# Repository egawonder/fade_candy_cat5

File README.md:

# fade_candy_cat5

When building the pirate ship bar I wanted to run RGB LEDs all around the ship.  Of course, this didn't initially work because of SI issues. I used braided pairs to solve this but thought there's got to be a better way.  This is the 80% better way. The RJ45 way.

Here I use one pair from the Cat-5 cable for signal and ground and the rest are just single ground wires. The pair is selected by jumper.  In practice, I think we just set all jumpers to use all of the pairs in parallel.

## Usage

For each LED strand (Fade Candy output) run the signal and ground to one board.  Connect a network cable to another board and the LEDs to the second board.  Route beefy power/ground to the second and set the same jumpers on each board. Victory.

## Improvements

I have a *much* better version but I haven't built it yet since this just works.  I'm going to though and when I verify that it's working I'll publish that, too.

The improved version routes power and ground in addition to the signal to each endpoint.  The main board injects power and gives you 8 RJ45 output ports.  The mating receiver board breaks out signal, power and ground to the LED strip.

Do that, not this. This was hacked together just before Halloween back in 2019? Yeah, 2019.   

## License

Released under CC0-1.0-Universal. See LICENSE

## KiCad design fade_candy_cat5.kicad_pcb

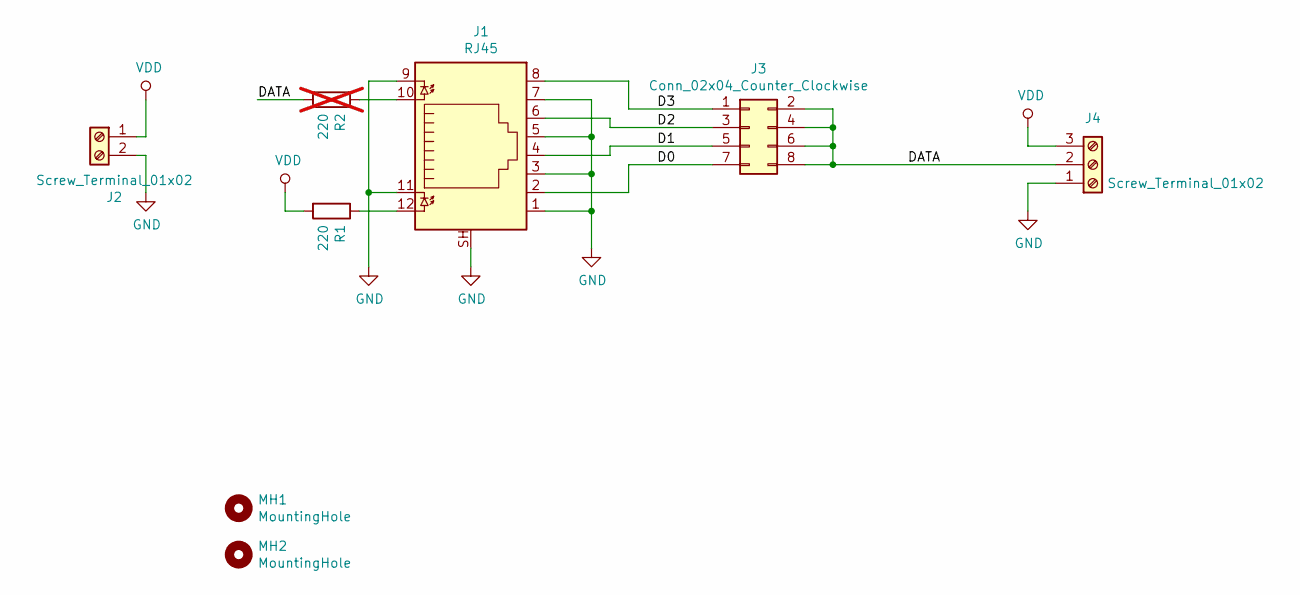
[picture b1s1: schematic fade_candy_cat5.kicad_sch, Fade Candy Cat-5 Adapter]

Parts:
J1: RJ45; RCH-56-31
J2: Screw_Terminal_01x02; WJ300V-5.0-2P
J3: Conn_02x04_Counter_Clockwise; PinHeader_2x04_P2.54mm_Vertical
J4: Screw_Terminal_01x02; WJ300V-5.0-3P
MH1, MH2: MountingHole; MountingHole_2.5mm
R1: 220; R_0603_1608Metric_Pad1.05x0.95mm_HandSolder
R2: 220; R_0603_1608Metric_Pad1.05x0.95mm_HandSolder; not fitted

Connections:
/D0: J1.2, J3.7
/D1: J1.4, J3.5
/D2: J1.6, J3.3
/D3: J1.8, J3.1
/DATA: J3.2, J3.4, J3.6, J3.8, J4.2, R2.2
GND: J1.1, J1.3, J1.5, J1.7, J1.9, J1.11, J1.SH, J2.2, J4.1
unnamed: J1.10, R2.1
unnamed: J1.12, R1.1
VDD: J2.1, J4.3, R1.2

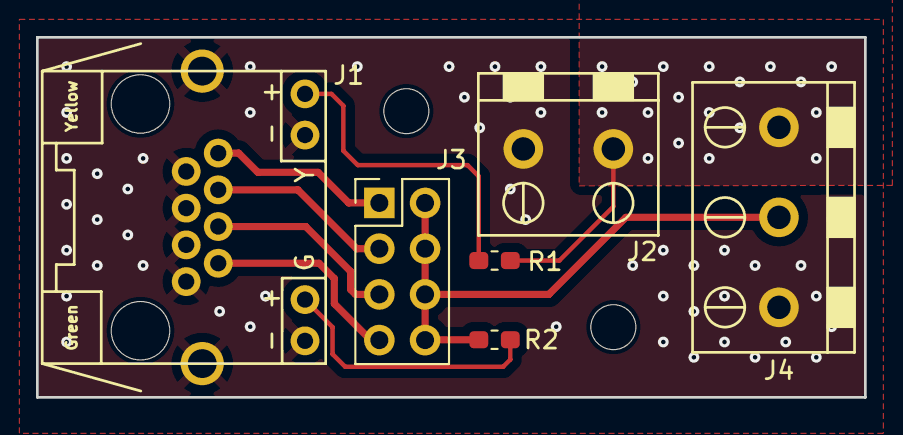
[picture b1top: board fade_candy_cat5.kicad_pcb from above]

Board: 2 copper layers, 46.0 x 20.0 mm, 8 parts (0 on the bottom side), 9 nets.

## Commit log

2024-09-13 Now with files

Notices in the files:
fade_candy_cat5.kicad_pcb:
(c) 2018
